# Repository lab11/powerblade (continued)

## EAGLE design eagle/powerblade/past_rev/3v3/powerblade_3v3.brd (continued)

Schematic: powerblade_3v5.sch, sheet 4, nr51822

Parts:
B1: BAL-NRF01D3
C11: 4.7uF; C0402; DIGIKEY 445-5947-1-ND
C12, C20: 1nF; 0402_CAP; DIGIKEY 490-1303-1-ND
C17: 1uF; 0402_CAP; DIGIKEY 1276-1513-1-ND
C18, C19: 12pF; 0402_CAP; DIGIKEY 490-6197-1-ND
C21: 47nF; 0402_CAP; DIGIKEY 445-1264-1-ND
C22: 2.2nF; 0402_CAP; DIGIKEY 490-5419-1-ND
C23: 0.8pF; 0402_CAP; DIGIKEY 490-6269-1-ND
C24: 0.1uF; C0402; DIGIKEY 445-4952-1-ND
J4: TC2030-JLINK-NL; TC2030-IDC-NL; DIGIKEY NP
L2: 15nH; 0402_CAP; DIGIKEY 587-1521-1-ND
L4: 10uH; C0603_TN; DIGIKEY 490-4025-1-ND
Q1: NTS4173; SC-70-3
R4: 12k; 0402_RES; DIGIKEY RHM12.0KCDCT-ND
R8: 220k; R0402_SM; DIGIKEY P220KJCT-ND
U4: NRF51822QF; QFN-48-6MM
X1: 16MHz; TXC-8Y; DIGIKEY 887-2003-1-ND
Y1: UREACH_XTEND

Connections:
+3V3: Q1.P2 (S), R8.2; also elsewhere on the board
AVDD: C12.1, C17.1, L2.1, U4.35 (AVDD), U4.36 (AVDD)
BLE_ENABLE: Q1.P1 (G), R8.1; also elsewhere on the board
BLE_LPINT: U4.9 (P05/AIN6); also elsewhere on the board
DCC: L4.2, U4.2 (DCC)
FROMBLE_RX: U4.48 (P29); also elsewhere on the board
unnamed: B1.SE, C23.1, Y1.P1
unnamed: B1.ANT1, U4.31 (ANT1)
unnamed: B1.ANT2, U4.32 (ANT2)
unnamed: L2.2, L4.1
unnamed: C18.1, U4.37 (XC1), X1.1
unnamed: C19.1, U4.38 (XC2), X1.3 (2)
unnamed: C20.1, U4.39 (DEC1)
unnamed: C21.1, U4.29 (DEC2)
SWDCLK: J4.4 (SWCLK), R4.1, U4.24 (SWDCLK)
SWDIO/!RESET: J4.2 (SWDIO), U4.23 (SWDIO/!RESET)
TOBLE_TX: U4.47 (P28); also elsewhere on the board
V+: C11.1, C24.1, J4.1 (VCC), Q1.P3 (D), U4.1 (VDD), U4.12 (VDD)
VDD_PA: B1.VCC (VDD_PA), C22.1, U4.30 (VDD_PA)

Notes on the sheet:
PIN12
PIN1
PIN36

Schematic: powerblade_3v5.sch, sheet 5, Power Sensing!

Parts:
C2: 0.1uF; C0402; DIGIKEY 490-10777-1-ND
C13: 0.1uF; 0402_CAP; DIGIKEY 445-4952-1-ND
C27, C38: 0.1uF; C0402; DIGIKEY 445-4952-1-ND
C39: 1.5uF; C0402; DIGIKEY 445-13815-1-ND
L3: L-USL0805; L0805; DIGIKEY 732-3452-1-ND
Q4: 2SK1829; SC-70-3
R2: 3k; R0402_SM; DIGIKEY P3.00KLCT-ND
R6: 660k; R0402; DIGIKEY P665KLCT-ND
R14: 200; R0402; DIGIKEY P200LCT-ND
R15, R20, R40: 1M 1%; R0402; DIGIKEY P1.00MLCT-ND
R16: 75 1%; R0402; DIGIKEY P75.0LCT-ND
R17: 1k 1%; R0402; DIGIKEY P1.00KLCT-ND
R18: 4.99 1%; R0402; DIGIKEY RMCF0402FT4R99CT-ND
R21: 1M 1%; R0402_SM; DIGIKEY P1.00MLCT-ND
R35: 20k; R0402; DIGIKEY P20.0KLCT-ND
R37: 887k 1%; R0402; DIGIKEY P887KLCT-ND
R38: 30k 1%; R0402; DIGIKEY P30.0KLCT-ND
R39: 16k 1%; R0402; DIGIKEY P16.0KLCT-ND
RF: 4.99k 1%; R0402; DIGIKEY P4.99KLCT-ND
RI1, RI2: 953k 1%; R0402; DIGIKEY P953KLCT-ND
U2: MCP6V3; SC70-5; DIGIKEY 296-19547-1-ND
U6: MAX9910; SC70-5; DIGIKEY 296-25252-1-ND
U7: OPA2369; SOT-23-8

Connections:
+3V3: C13.1, C27.1, C38.1, R15.1, R20.2, R40.2, U2.P5 (VCC), U6.P5 (VCC), U7.P8 (VCC); also elsewhere on the board
METER_ENABLE: Q4.P1 (G), R6.1; also elsewhere on the board
unnamed: R2.1, R37.2, U7.P7 (OUT)
unnamed 20: L3.2, R14.1, R15.2, R16.2; also elsewhere on the board
unnamed: L3.1, R14.2, U2.P1 (IN+)
unnamed: R20.1, R21.2, U6.P1 (IN+)
unnamed: RF.1, RI1.2, RI2.2, U6.P3 (IN-)
unnamed 25: R17.1, R18.2, U2.P3 (IN-); also elsewhere on the board
unnamed: R37.1, R38.2, U7.P6 (IN-)
unnamed: R35.1, U7.P1 (OUT), U7.P2 (IN-)
unnamed: R39.2, R40.1, U7.P3 (IN+)
VAMP: C39.1, R17.2, U2.P4 (OUT)
VFILT: C39.2, R35.2, U7.P5 (IN+); also elsewhere on the board
VTEST: RI1.1; also elsewhere on the board

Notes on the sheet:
Voltage offset
50uV offset
For zero offset:
R15=NP
R16=0
Current Measurement
Voltage Measurement
Output voltage:
-(RF/RI)*VTEST + VCC/2
R15=1M
R16=15

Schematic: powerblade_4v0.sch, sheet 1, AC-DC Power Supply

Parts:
C1: 33uF; CPOL0805_SM; DIGIKEY 478-8650-1-ND
C3: 22uF; C0603_SM; DIGIKEY 445-9077-1-ND
D1: ZENERBZT52; BZT52; DIGIKEY BZT52C10T-7DICT-ND
D2: DIODE; BAS521
J2: AC_INFINAL; AC3_FINAL; DIGIKEY ED1649-ND
R3: 69.8k; R1210; DIGIKEY P69.8KAACT-ND

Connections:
VCC: C1.+, C3.1, D2.C; also elsewhere on the board
VTEST: J2.PA.3, R3.1; also elsewhere on the board
ZC: D1.C, D2.A, R3.2; also elsewhere on the board

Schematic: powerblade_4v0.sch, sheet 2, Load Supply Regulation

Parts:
C4: 22pF; C0402; DIGIKEY 445-1239-1-ND
C5: NP; C0603_TN; DIGIKEY NP
C7: 4.7uF; C0402; DIGIKEY 445-8023-1-ND
C8: 0.1uF; C0402; DIGIKEY 445-4952-1-ND
C9: 0.1uF; C0402_SM; DIGIKEY 445-4952-1-ND
C10: 22uF; C0603_SM; DIGIKEY 445-9077-1-ND
L1: 10uH; L0805; DIGIKEY 490-4990-1-ND
R7: 560k; R0402; DIGIKEY P560KLCT-ND
R9: 180k; R0402; DIGIKEY P180KLCT-ND
R24: 1 1%; R0603_SM; DIGIKEY P1.0AJCT-ND
U1: TPS62122; WDFN-6

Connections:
+3V3: C5.1, R24.2; also elsewhere on the board
unnamed: L1.2, U1.P1 (SW)
unnamed: C4.2, R7.1, R9.2, U1.P3 (FB)
VCC: C7.1, C8.1, U1.P4 (EN), U1.P5 (VIN); also elsewhere on the board
VS+: C4.1, C9.1, C10.1, L1.1, R7.2, R24.1, U1.P2 (VOUT); also elsewhere on the board

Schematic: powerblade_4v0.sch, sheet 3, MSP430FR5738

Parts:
C6, C34: 8pF; C0402; DIGIKEY 445-4890-1-ND
C14: 0.1uF; C0402; DIGIKEY 445-4952-1-ND
C15: 10uF; C0603_SM; DIGIKEY 445-6853-1-ND
C16: 470nF; C0402; DIGIKEY 445-4989-1-ND
J1: JTAG_14PIN_IDC-ND; TC2050-IDC-NL-430-ND; DIGIKEY NP
R11, R22: 670k; R0402; DIGIKEY P665KLCT-ND
R12, R13: 330k; R0402; DIGIKEY P330KLCT-ND
R19: 47k; R0402; DIGIKEY P47KJCT-ND
U3: MSP430FR5738; VQFN-24
X3: 32.768kHz; 0805; DIGIKEY 535-12373-1-ND

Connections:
+3V3: C14.1, C15.1, J1.P2 (2), R19.2, U3.P20 (DVCC), U3.P24 (AVCC); also elsewhere on the board
BLE_ENABLE: U3.P16 (P1.6/TA0.0/UCBSDA/MOSI); also elsewhere on the board
BLE_LPINT: U3.P17 (P1.7/TA1.0/UCBSCL/MISO); also elsewhere on the board
FROMBLE_RX: U3.P14 (P2.1/TB0.0/UCARX/MISO); also elsewhere on the board
METER_ENABLE: U3.P15 (P2.2/UCBCLK); also elsewhere on the board
unnamed: C34.2, U3.P22 (XOUT), X3.1
unnamed: C16.2, U3.P18 (VCORE)
unnamed: C6.2, U3.P21 (XIN), X3.2
PWM_CURRENT: U3.P3 (P1.2/TA1.1/A2); also elsewhere on the board
PWM_VOLTAGE: U3.P4 (P1.3/TA1.2/A3); also elsewhere on the board
RST: J1.P10 (11), R19.1, U3.P12 (RST)
TCK: J1.P7 (7), U3.P10 (TCK)
TDI: J1.P3 (3), U3.P8 (TDI)
TDO: J1.P1 (1), R13.2, R22.1, U3.P7 (TDO)
TEST: J1.P8 (8), U3.P11 (TEST)
TMS: J1.P5 (5), U3.P9 (TMS)
TOBLE_TX: U3.P13 (P2.0/UCATX/MOSI); also elsewhere on the board
VCC: R11.2; also elsewhere on the board
VCC_SENSE: R11.1, R12.2, U3.P6 (P1.5/TB0.2/UCACLK)
VFILT: U3.P2 (P1.1/VREF+); also elsewhere on the board
ZC: R22.2; also elsewhere on the board

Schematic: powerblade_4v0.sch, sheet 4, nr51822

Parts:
B1: BAL-NRF01D3
C11: 4.7uF; C0402; DIGIKEY 445-5947-1-ND
C12, C20: 1nF; 0402_CAP; DIGIKEY 490-1303-1-ND
C17: 1uF; 0402_CAP; DIGIKEY 1276-1513-1-ND
C18, C19: 12pF; 0402_CAP; DIGIKEY 490-6197-1-ND
C21: 47nF; 0402_CAP; DIGIKEY 445-1264-1-ND
C22: 2.2nF; 0402_CAP; DIGIKEY 490-5419-1-ND
C23: 0.8pF; 0402_CAP; DIGIKEY 490-6269-1-ND
C24: 0.1uF; C0402; DIGIKEY 445-4952-1-ND
J4: TC2030-JLINK-NL; TC2030-IDC-NL; DIGIKEY NP
L2: 15nH; 0402_CAP; DIGIKEY 587-1521-1-ND
L4: 10uH; C0603_TN; DIGIKEY 490-4025-1-ND
Q1: NTS4173; SC-70-3
R4: 12k; 0402_RES; DIGIKEY RHM12.0KCDCT-ND
R8: 220k; R0402_SM; DIGIKEY P220KJCT-ND
U4: NRF51822QF; QFN-48-6MM
X1: 16MHz; TXC-8Y; DIGIKEY 887-2003-1-ND
Y1: UREACH_XTEND

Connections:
+3V3: Q1.P2 (S), R8.2; also elsewhere on the board
AVDD: C12.1, C17.1, L2.1, U4.35 (AVDD), U4.36 (AVDD)
BLE_ENABLE: Q1.P1 (G), R8.1; also elsewhere on the board
BLE_LPINT: U4.9 (P05/AIN6); also elsewhere on the board
DCC: L4.2, U4.2 (DCC)
FROMBLE_RX: U4.48 (P29); also elsewhere on the board
unnamed: B1.SE, C23.1, Y1.P1
unnamed: B1.ANT1, U4.31 (ANT1)
unnamed: B1.ANT2, U4.32 (ANT2)
unnamed: L2.2, L4.1
unnamed: C18.1, U4.37 (XC1), X1.1
unnamed: C19.1, U4.38 (XC2), X1.3 (2)
unnamed: C20.1, U4.39 (DEC1)
unnamed: C21.1, U4.29 (DEC2)
SWDCLK: J4.4 (SWCLK), R4.1, U4.24 (SWDCLK)
SWDIO/!RESET: J4.2 (SWDIO), U4.23 (SWDIO/!RESET)
TOBLE_TX: U4.47 (P28); also elsewhere on the board
V+: C11.1, C24.1, J4.1 (VCC), Q1.P3 (D), U4.1 (VDD), U4.12 (VDD)
VDD_PA: B1.VCC (VDD_PA), C22.1, U4.30 (VDD_PA)

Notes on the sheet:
PIN12
PIN1
PIN36

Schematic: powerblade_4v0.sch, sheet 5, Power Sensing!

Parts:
C2: 0.1uF; C0402; DIGIKEY 490-10777-1-ND
C13: 0.1uF; 0402_CAP; DIGIKEY 445-4952-1-ND
C27, C38: 0.1uF; C0402; DIGIKEY 445-4952-1-ND
C39: 1.5uF; C0402; DIGIKEY 445-13815-1-ND
L3: L-USL0805; L0805; DIGIKEY 732-3452-1-ND
Q4: 2SK1829; SC-70-3
R2: 3k; R0402_SM; DIGIKEY P3.00KLCT-ND
R6: 660k; R0402; DIGIKEY P665KLCT-ND
R14: 200; R0402; DIGIKEY P200LCT-ND
R15, R20, R40: 1M 1%; R0402; DIGIKEY P1.00MLCT-ND
R16: 75 1%; R0402; DIGIKEY P75.0LCT-ND
R17: 1k 1%; R0402; DIGIKEY P1.00KLCT-ND
R18: 4.99 1%; R0402; DIGIKEY RMCF0402FT4R99CT-ND
R21: 1M 1%; R0402_SM; DIGIKEY P1.00MLCT-ND
R35: 20k; R0402; DIGIKEY P20.0KLCT-ND
R37: 887k 1%; R0402; DIGIKEY P887KLCT-ND
R38: 30k 1%; R0402; DIGIKEY P30.0KLCT-ND
R39: 16k 1%; R0402; DIGIKEY P16.0KLCT-ND
RF: 4.99k 1%; R0402; DIGIKEY P4.99KLCT-ND
RI1, RI2: 953k 1%; R0402; DIGIKEY P953KLCT-ND
U2: MCP6V3; SC70-5; DIGIKEY 296-19547-1-ND
U6: MAX9910; SC70-5; DIGIKEY 296-25252-1-ND
U7: OPA2369; SOT-23-8

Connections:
+3V3: C13.1, C27.1, C38.1, R15.1, R20.2, R40.2, U2.P5 (VCC), U6.P5 (VCC), U7.P8 (VCC); also elsewhere on the board
METER_ENABLE: Q4.P1 (G), R6.1; also elsewhere on the board
unnamed: R2.1, R37.2, U7.P7 (OUT)
unnamed 20: L3.2, R14.1, R15.2, R16.2; also elsewhere on the board
unnamed: L3.1, R14.2, U2.P1 (IN+)
unnamed: R20.1, R21.2, U6.P1 (IN+)
unnamed: RF.1, RI1.2, RI2.2, U6.P3 (IN-)
unnamed 25: R17.1, R18.2, U2.P3 (IN-); also elsewhere on the board
unnamed: R37.1, R38.2, U7.P6 (IN-)
unnamed: R35.1, U7.P1 (OUT), U7.P2 (IN-)
unnamed: R39.2, R40.1, U7.P3 (IN+)
VAMP: C39.1, R17.2, U2.P4 (OUT)
VFILT: C39.2, R35.2, U7.P5 (IN+); also elsewhere on the board
VTEST: RI1.1; also elsewhere on the board

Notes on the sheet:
Voltage offset
50uV offset
For zero offset:
R15=NP
R16=0
Current Measurement
Voltage Measurement
Output voltage:
-(RF/RI)*VTEST + VCC/2
R15=1M
R16=15

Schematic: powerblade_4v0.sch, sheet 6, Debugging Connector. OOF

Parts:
SV1: MA12-11M27; MA12-1_1MM27; DIGIKEY S9014E-12-ND

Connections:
+3V3: SV1.P8 (8); also elsewhere on the board
FROMBLE_RX: SV1.P2 (2); also elsewhere on the board
PWM_CURRENT: SV1.P5 (5); also elsewhere on the board
PWM_VOLTAGE: SV1.P4 (4); also elsewhere on the board
TOBLE_TX: SV1.P1 (1); also elsewhere on the board
VCC: SV1.P10 (10); also elsewhere on the board
VFILT: SV1.P9 (9); also elsewhere on the board
VS+: SV1.P12 (12); also elsewhere on the board
ZC: SV1.P11 (11); also elsewhere on the board

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
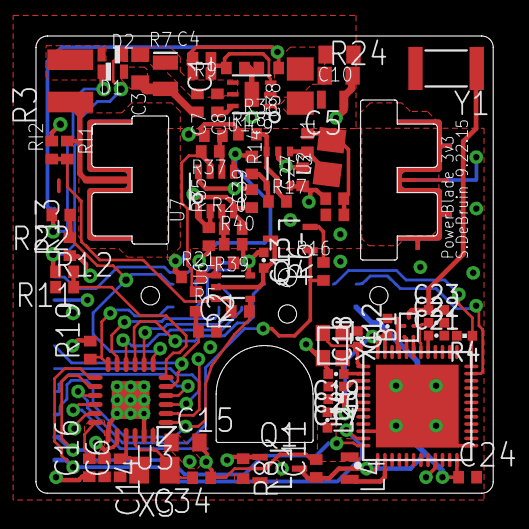
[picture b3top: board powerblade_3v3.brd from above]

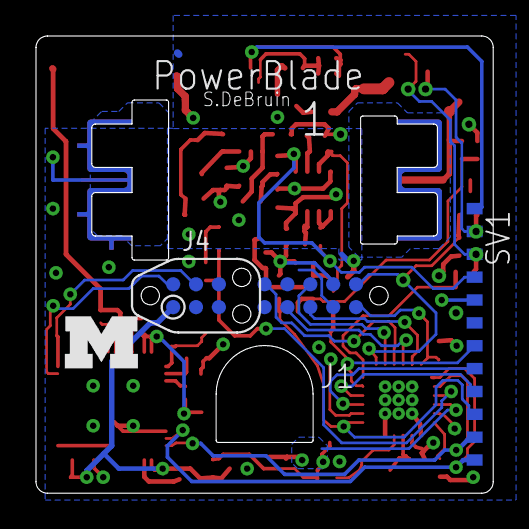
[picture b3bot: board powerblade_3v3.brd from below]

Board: 4 copper layers, 25.4 x 25.4 mm, 79 parts (4 on the bottom side), 53 nets.

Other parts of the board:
U$1: BLOCK-M

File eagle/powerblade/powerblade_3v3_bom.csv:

"Part";"Value";"Device";"Package";"Description";"DIGIKEY";"DIGIKEY_2";"DIGIKEY_3";"DIGIKEY_4";"FRACTUS";"MOUSER";
"B1";"BAL-NRF01D3";"BAL-NRF01D3";"BAL-NRF01D3";"50 ohm nominal input / conjugate match balun to nRF51422-QFAA,";"497-13637-1-ND";"";"";"";"";"511-BAL-NRF01D3";
"C1";"33uF";"CPOL-US0805_SM";"CPOL0805_SM";"POLARIZED CAPACITOR, American symbol";"478-8650-1-ND";"";"";"";"";"";
"C2";"0.1uF";"C-EUC0402";"C0402";"CAPACITOR, European symbol";"490-10777-1-ND";"";"";"";"";"";
"C3";"22uF";"C-EUC0603_SM";"C0603_SM";"CAPACITOR, European symbol";"445-9077-1-ND";"";"";"";"";"";
"C4";"22pF";"C-EUC0402";"C0402";"CAPACITOR, European symbol";"445-1239-1-ND";"";"";"";"";"";
"C5";"NP";"C-EUC0603_TN";"C0603_TN";"CAPACITOR, European symbol";"NP";"";"";"";"";"";
"C6";"8pF";"C-EUC0402";"C0402";"CAPACITOR, European symbol";"445-4890-1-ND";"";"";"";"";"";
"C7";"4.7uF";"C-EUC0402";"C0402";"CAPACITOR, European symbol";"445-8023-1-ND";"";"";"";"";"";
"C8";"0.1uF";"C-EUC0402";"C0402";"CAPACITOR, European symbol";"445-4952-1-ND";"";"";"";"";"";
"C9";"0.1uF";"C-EUC0402_SM";"C0402_SM";"CAPACITOR, European symbol";"445-4952-1-ND";"";"";"";"";"";
"C10";"22uF";"C-EUC0603_SM";"C0603_SM";"CAPACITOR, European symbol";"445-9077-1-ND";"";"";"";"";"";
"C11";"4.7uF";"C-EUC0402";"C0402";"CAPACITOR, European symbol";"445-5947-1-ND";"";"";"";"";"";
"C12";"1nF";"CAPACITOR";"0402_CAP";"0402 Capacitor";"490-1303-1-ND";"";"";"";"";"";
"C13";"0.1uF";"CAPACITOR";"0402_CAP";"0402 Capacitor";"445-4952-1-ND";"";"";"";"";"";
"C14";"0.1uF";"C-EUC0402";"C0402";"CAPACITOR, European symbol";"445-4952-1-ND";"";"";"";"";"";
"C15";"10uF";"C-EUC0603_SM";"C0603_SM";"CAPACITOR, European symbol";"445-6853-1-ND";"";"";"";"";"";
"C16";"470nF";"C-EUC0402";"C0402";"CAPACITOR, European symbol";"445-4989-1-ND";"";"";"";"";"";
"C17";"1uF";"CAPACITOR";"0402_CAP";"0402 Capacitor";"1276-1513-1-ND";"";"";"";"";"";
"C18";"12pF";"CAPACITOR";"0402_CAP";"0402 Capacitor";"490-6197-1-ND";"";"";"";"";"";
"C19";"12pF";"CAPACITOR";"0402_CAP";"0402 Capacitor";"490-6197-1-ND";"";"";"";"";"";
"C20";"1nF";"CAPACITOR";"0402_CAP";"0402 Capacitor";"490-1303-1-ND";"";"";"";"";"";
"C21";"47nF";"CAPACITOR";"0402_CAP";"0402 Capacitor";"445-1264-1-ND";"";"";"";"";"";
"C22";"2.2nF";"CAPACITOR";"0402_CAP";"0402 Capacitor";"490-5419-1-ND";"";"";"";"";"";
"C23";"0.8pF";"CAPACITOR";"0402_CAP";"0402 Capacitor";"490-6269-1-ND";"";"";"";"";"";
"C24";"0.1uF";"C-EUC0402";"C0402";"CAPACITOR, European symbol";"445-4952-1-ND";"";"";"";"";"";
"C27";"0.1uF";"C-EUC0402";"C0402";"CAPACITOR, European symbol";"445-4952-1-ND";"";"";"";"";"";
"C34";"8pF";"C-EUC0402";"C0402";"CAPACITOR, European symbol";"445-4890-1-ND";"";"";"";"";"";
"C38";"0.1uF";"C-EUC0402";"C0402";"CAPACITOR, European symbol";"445-4952-1-ND";"";"";"";"";"";
"C39";"1.5uF";"C-EUC0402";"C0402";"CAPACITOR, European symbol";"445-13815-1-ND";"";"";"";"";"";
"D1";"ZENERBZT52";"ZENERBZT52";"BZT52";"";"BZT52C10T-7DICT-ND ";"";"";"";"";"";
"D2";"DIODE";"DIODE";"BAS521";"";"BAS521-7DICT-ND";"";"";"";"";"";
"J1";"JTAG_14PIN_IDC-ND";"JTAG_14PIN_IDC-ND";"TC2050-IDC-NL-430-ND";"";"NP";"";"";"";"";"";
"J2";"AC_INF45";"AC_INF45";"AC3_F45";"";"ED1649-ND";"ED1649-ND";"ED1649-ND";"ED1649-ND";"";"";
"J4";"TC2030-JLINK-NL";"TC2030-JLINK-NL";"TC2030-IDC-NL";"";"NP";"";"";"";"";"";
"L1";"10uH";"L-USL0805";"L0805";"INDUCTOR, American symbol";"490-4990-1-ND";"";"";"";"";"";
"L2";"15nH";"INDUCTOR0402";"0402_CAP";"";"587-1521-1-ND";"";"";"";"";"";
"L3";"";"L-USL0805";"L0805";"INDUCTOR, American symbol";"732-3452-1-ND";"";"";"";"";"";
"L4";"10uH";"L-USL0603_TN";"C0603_TN";"INDUCTOR, American symbol";"490-4025-1-ND";"";"";"";"";"";
"Q1";"NTS4173";"NTS4173";"SC-70-3";"";"NTS4173PT1GOSCT-ND";"";"";"";"";"";
"Q4";"2SK1829";"2SK1829";"SC-70-3";"";"2SK1829TE85LFCT-ND";"";"";"";"";"";
"R2";"3k";"R-US_R0402_SM";"R0402_SM";"RESISTOR, American symbol";"P3.00KLCT-ND";"";"";"";"";"";
"R3";"69.8k";"R-US_R1210";"R1210";"RESISTOR, American symbol";"P69.8KAACT-ND";"";"";"";"";"";
"R4";"12k";"RESISTOR";"0402_RES";"Resistor";"RHM12.0KCDCT-ND";"";"";"";"";"";
"R6";"660k";"R-US_R0402";"R0402";"RESISTOR, American symbol";"P665KLCT-ND";"";"";"";"";"";
"R7";"560k";"R-US_R0402";"R0402";"RESISTOR, American symbol";"P560KLCT-ND";"";"";"";"";"";
"R8";"220k";"R-US_R0402_SM";"R0402_SM";"RESISTOR, American symbol";"P220KJCT-ND";"";"";"";"";"";
"R9";"180k";"R-US_R0402";"R0402";"RESISTOR, American symbol";"P180KLCT-ND";"";"";"";"";"";
"R11";"670k";"R-US_R0402";"R0402";"RESISTOR, American symbol";"P665KLCT-ND";"";"";"";"";"";
"R12";"330k";"R-US_R0402";"R0402";"RESISTOR, American symbol";"P330KLCT-ND";"";"";"";"";"";
"R13";"330k";"R-US_R0402";"R0402";"RESISTOR, American symbol";"P330KLCT-ND";"";"";"";"";"";
"R14";"200";"R-US_R0402";"R0402";"RESISTOR, American symbol";"P200LCT-ND";"";"";"";"";"";
"R15";"1M 1%";"R-US_R0402";"R0402";"RESISTOR, American symbol";"P1.00MLCT-ND";"";"";"";"";"";
"R16";"75 1%";"R-US_R0402";"R0402";"RESISTOR, American symbol";"P75.0LCT-ND";"";"";"";"";"";
"R17";"1k 1%";"R-US_R0402";"R0402";"RESISTOR, American symbol";"P1.00KLCT-ND";"";"";"";"";"";
"R18";"4.99 1%";"R-US_R0402";"R0402";"RESISTOR, American symbol";"RMCF0402FT4R99CT-ND";"";"";"";"";"";
"R19";"47k";"R-US_R0402";"R0402";"RESISTOR, American symbol";"P47KJCT-ND";"";"";"";"";"";
"R20";"1M 1%";"R-US_R0402";"R0402";"RESISTOR, American symbol";"P1.00MLCT-ND";"";"";"";"";"";
"R21";"1M 1%";"R-US_R0402_SM";"R0402_SM";"RESISTOR, American symbol";"P1.00MLCT-ND";"";"";"";"";"";
"R22";"670k";"R-US_R0402";"R0402";"RESISTOR, American symbol";"P665KLCT-ND";"";"";"";"";"";
"R24";"1 1%";"R-US_R0603_SM";"R0603_SM";"RESISTOR, American symbol";"P1.0AJCT-ND";"";"";"";"";"";
"R35";"20k";"R-US_R0402";"R0402";"RESISTOR, American symbol";"P20.0KLCT-ND";"";"";"";"";"";
"R37";"887k 1%";"R-US_R0402";"R0402";"RESISTOR, American symbol";"P887KLCT-ND";"";"";"";"";"";
"R38";"30k 1%";"R-US_R0402";"R0402";"RESISTOR, American symbol";"P30.0KLCT-ND";"";"";"";"";"";
"R39";"16k 1%";"R-US_R0402";"R0402";"RESISTOR, American symbol";"P16.0KLCT-ND";"";"";"";"";"";
"R40";"1M 1%";"R-US_R0402";"R0402";"RESISTOR, American symbol";"P1.00MLCT-ND";"";"";"";"";"";
"RF";"4.99k 1%";"R-US_R0402";"R0402";"RESISTOR, American symbol";"P4.99KLCT-ND";"";"";"";"";"";
"RI1";"953k 1%";"R-US_R0402";"R0402";"RESISTOR, American symbol";"P953KLCT-ND";"";"";"";"";"";
"RI2";"953k 1%";"R-US_R0402";"R0402";"RESISTOR, American symbol";"P953KLCT-ND";"";"";"";"";"";
"SV1";"";"MA12-11M27";"MA12-1_1MM27";"PIN HEADER";"S9014E-12-ND";"";"";"";"";"";
"U1";"TPS62122";"TPS62122";"WDFN-6";"";"296-27695-1-ND";"";"";"";"";"";
"U2";"MCP6V3";"MCP6V3";"SC70-5";"";"296-19547-1-ND";"";"";"";"";"";
"U3";"MSP430FR5738";"MSP430FR5738";"VQFN-24";"";"296-29232-1-ND";"";"";"";"";"";
"U4";"NRF51822QF";"NRF51822QF";"QFN-48-6MM";"Multiprotocol Bluetooth® 4.0 low energy/2.4 GHz RF SoC";"1490-1032-1-ND";"";"";"";"";"949-NRF51822-QFAB-R7";
"U6";"MAX9910";"MAX9910";"SC70-5";"";"296-25252-1-ND";"";"";"";"";"";
"U7";"OPA2369";"OPA2369";"SOT-23-8";"";"296-22671-1-ND";"";"";"";"";"";
"X1";"16MHz";"TXC-8Y";"TXC-8Y";"2mmx1.6mm SMD Crystal";"887-2003-1-ND";"";"";"";"";"";
"X3";"32.768kHz";"CRYSTAL_0805";"0805";"";"535-12373-1-ND";"";"";"";"";"";
"Y1";"UREACH_XTEND";"UREACH_XTEND";"UREACH_XTEND";"";"";"";"";"";"FR05-S1-N-0-110";"";

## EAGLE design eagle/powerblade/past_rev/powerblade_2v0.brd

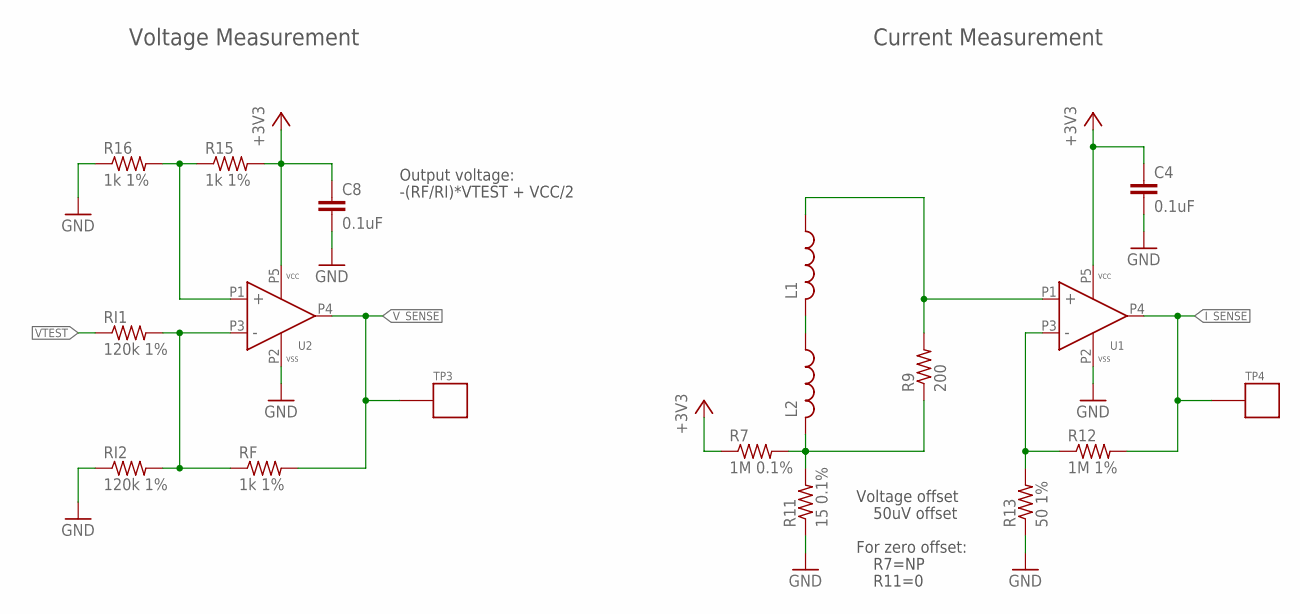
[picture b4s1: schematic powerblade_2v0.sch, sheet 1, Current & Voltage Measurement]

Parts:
C4, C8: 0.1uF; C0402; DIGIKEY 445-1265-1-ND
L1, L2: L-USL0805; L0805
R7: 1M 0.1%; R0603; DIGIKEY A102234CT-ND
R9: 200; R0603; DIGIKEY P200HCT-ND
R11: 15 0.1%; R0603; DIGIKEY A109933CT-ND
R12: 1M 1%; R0603; DIGIKEY A102234CT-ND
R13: 50 1%; R0603; DIGIKEY P49.9HCT-ND
R15, R16: 1k 1%; R0603; DIGIKEY P1.00KHCT-ND
RF: 1k 1%; R0603; DIGIKEY P1.00KHCT-ND
RI1, RI2: 120k 1%; R0603; DIGIKEY P120KHCT-ND
TP3, TP4: TP_STD; TP
U1, U2: MAX9910; SC70-5

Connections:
+3V3: C4.1, C8.1, R7.1, R15.2, U1.P5 (VCC), U2.P5 (VCC); also elsewhere on the board
GND: C4.2, C8.2, R11.1, R13.1, R16.1, RI2.1, U1.P2 (VSS), U2.P2 (VSS); also elsewhere on the board
I_SENSE: R12.2, TP4.P$1, U1.P4 (OUT); also elsewhere on the board
unnamed: R15.1, R16.2, U2.P1 (IN+)
unnamed: R12.1, R13.2, U1.P3 (IN-)
unnamed: RF.1, RI1.2, RI2.2, U2.P3 (IN-)
unnamed: L2.2, R7.2, R9.1, R11.2
unnamed: L1.1, R9.2, U1.P1 (IN+)
unnamed: L1.2, L2.1
VTEST: RI1.1; also elsewhere on the board
V_SENSE: RF.2, TP3.P$1, U2.P4 (OUT); also elsewhere on the board

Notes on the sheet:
Voltage offset
50uV offset
For zero offset:
R7=NP
R11=0
Current Measurement
Voltage Measurement
Output voltage:
-(RF/RI)*VTEST + VCC/2

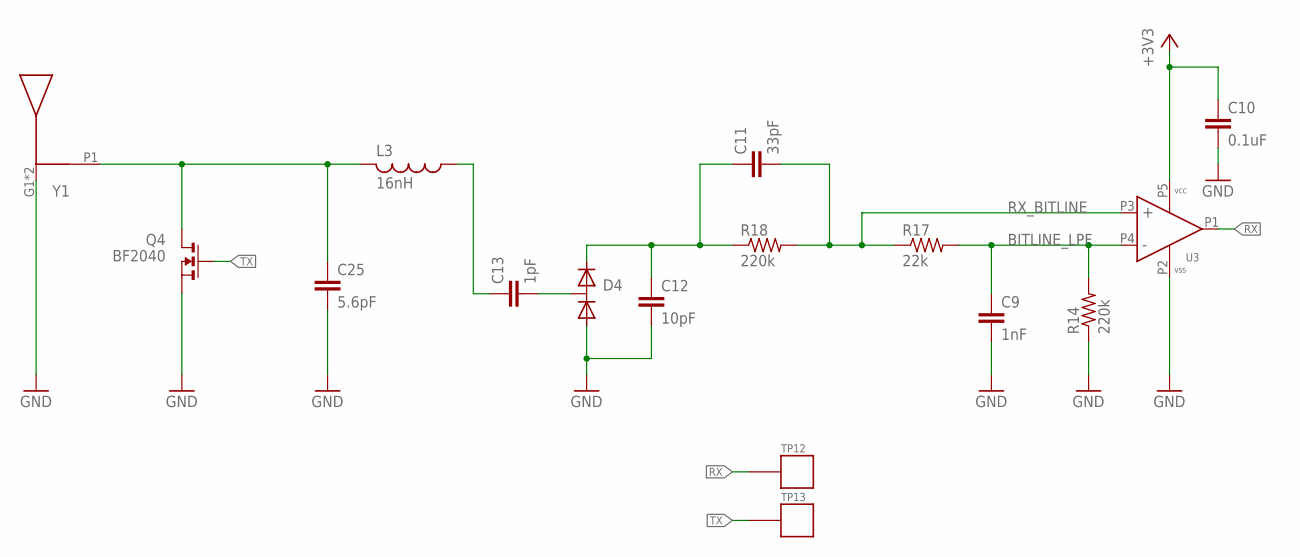
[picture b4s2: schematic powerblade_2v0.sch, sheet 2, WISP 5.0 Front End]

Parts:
C9: 1nF; C0603; DIGIKEY 490-6377-1-ND
C10: 0.1uF; C0603; DIGIKEY 445-1316-1-ND
C11: 33pF; C0603; DIGIKEY 399-7894-1-ND
C12: 10pF; C0603; DIGIKEY 1276-2151-1-ND
C13: 1pF; C0603; DIGIKEY 712-1323-1-ND
C25: 5.6pF; C0603; DIGIKEY 712-1360-1-ND
D4: HSMS-285C; SOT-323
L3: 16nH; L0603; DIGIKEY 732-1728-1-ND
Q4: BF2040; SOT-143
R14, R18: 220k; R0603; DIGIKEY P220KDBCT-ND
R17: 22k; R0603; DIGIKEY P22KDBCT-ND
TP12, TP13: TP_STD; TP
U3: NCS2200S; SC70-5
Y1: ANT-USP; DIGIKEY ANT-916-USP-ND

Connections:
+3V3: C10.1, U3.P5 (VCC); also elsewhere on the board
ANT: C25.1, L3.2, Q4.P2 (D), Y1.P1
BITLINE_LPF: C9.1, R14.2, R17.2, U3.P4 (IN-)
GND: C9.2, C10.2, C12.2, C25.2, D4.P1, Q4.P1 (S), R14.1, U3.P2 (VSS), Y1.G1 (G), Y1.G2 (G); also elsewhere on the board
unnamed: C13.1, L3.1
unnamed: C13.2, D4.P3
unnamed: C11.1, C12.1, D4.P2, R18.1
RX: TP12.P$1, U3.P1 (OUT); also elsewhere on the board
RX_BITLINE: C11.2, R17.1, R18.2, U3.P3 (IN+)
TX: Q4.P3 (G), Q4.P4 (G), TP13.P$1; also elsewhere on the board

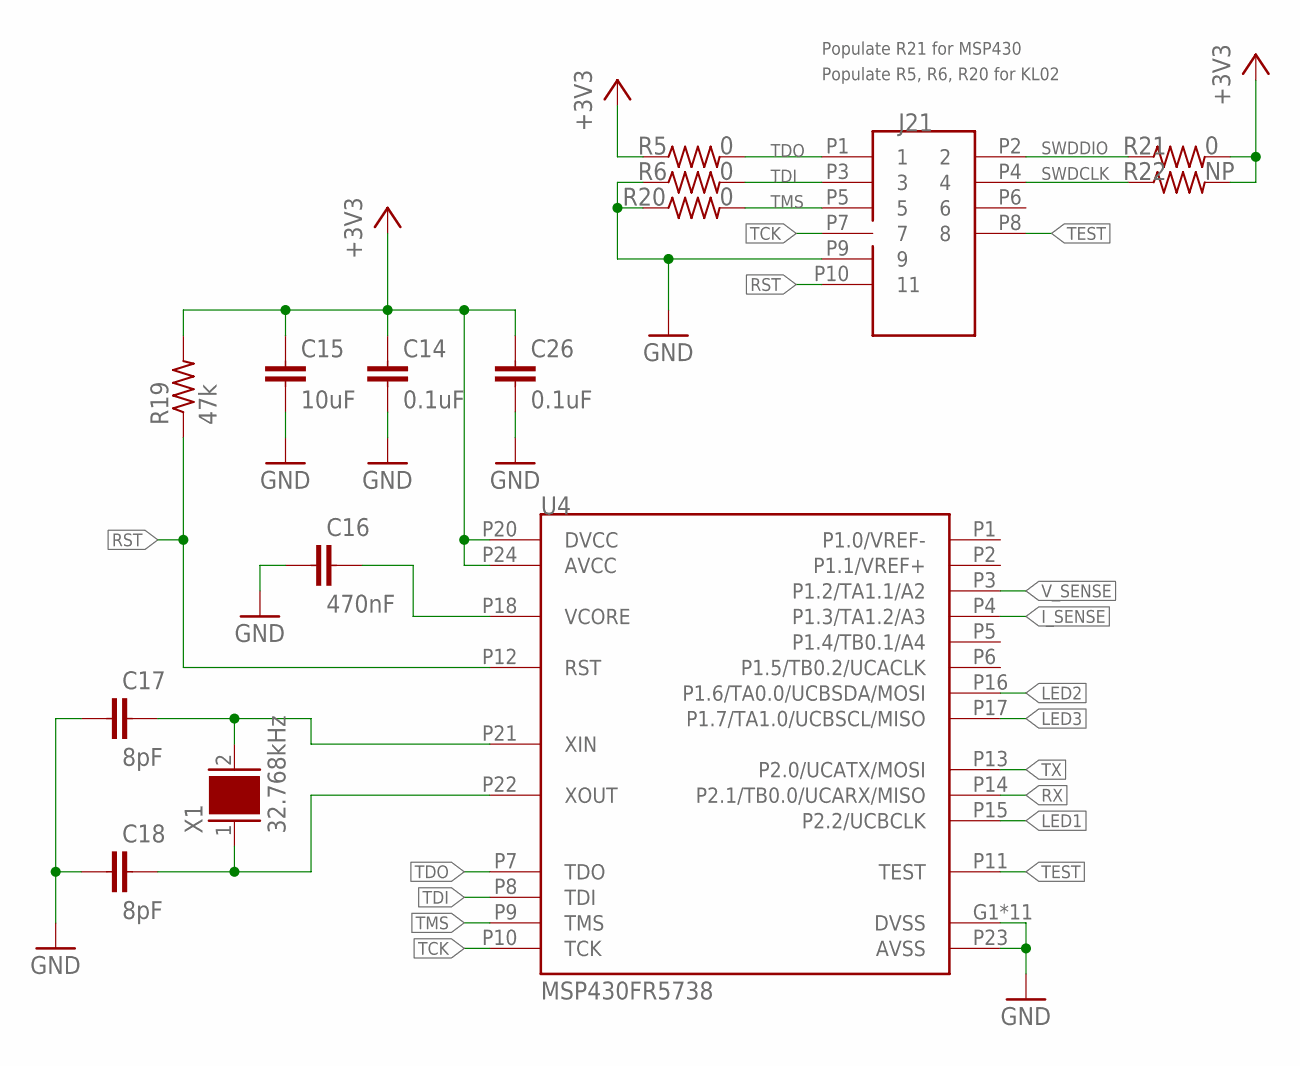
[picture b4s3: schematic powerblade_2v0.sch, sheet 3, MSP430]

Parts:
C14, C26: 0.1uF; C0603; DIGIKEY 445-1316-1-ND
C15: 10uF; C0603; DIGIKEY 1276-1119-1-ND
C16: 470nF; C0603; DIGIKEY 445-5192-1-ND
C17, C18: 8pF; C0603; DIGIKEY 1276-1817-1-ND
J21: JTAG_14PIN_IDC-NL; TC2050-IDC-NL-430; DIGIKEY NP
R5, R6, R20, R21: 0; R0603; DIGIKEY P0.0GCT-ND
R19: 47k; R0603; DIGIKEY P47KGCT-ND
R22: NP; R0603; DIGIKEY NP
U4: MSP430FR5738; VQFN-24
X1: 32.768kHz; 0805; DIGIKEY 535-12373-1-ND

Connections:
+3V3: C14.1, C15.1, C26.1, R5.1, R19.2, R21.2, R22.2, U4.P20 (DVCC), U4.P24 (AVCC); also elsewhere on the board
GND: C14.2, C15.2, C16.1, C17.1, C18.1, C26.2, J21.P9 (9), R6.1, R20.1, U4.G1 (DVSS), U4.G2 (DVSS), U4.G3 (DVSS), U4.G4 (DVSS), U4.G5 (DVSS), U4.G6 (DVSS), U4.G7 (DVSS), U4.G8 (DVSS), U4.G9 (DVSS), U4.P19 (DVSS), U4.P23 (AVSS), U4.PAD (DVSS); also elsewhere on the board
I_SENSE: U4.P4 (P1.3/TA1.2/A3); also elsewhere on the board
LED1: U4.P15 (P2.2/UCBCLK); also elsewhere on the board
LED2: U4.P16 (P1.6/TA0.0/UCBSDA/MOSI); also elsewhere on the board
LED3: U4.P17 (P1.7/TA1.0/UCBSCL/MISO); also elsewhere on the board
unnamed: C18.2, U4.P22 (XOUT), X1.1
unnamed: C16.2, U4.P18 (VCORE)
unnamed: C17.2, U4.P21 (XIN), X1.2
RST: J21.P10 (11), R19.1, U4.P12 (RST); also elsewhere on the board
RX: U4.P14 (P2.1/TB0.0/UCARX/MISO); also elsewhere on the board
SWDCLK: J21.P4 (4), R22.1; also elsewhere on the board
SWDDIO: J21.P2 (2), R21.1; also elsewhere on the board
TCK: J21.P7 (7), U4.P10 (TCK)
TDI: J21.P3 (3), R6.2, U4.P8 (TDI)
TDO: J21.P1 (1), R5.2, U4.P7 (TDO)
TEST: J21.P8 (8), U4.P11 (TEST)
TMS: J21.P5 (5), R20.2, U4.P9 (TMS)
TX: U4.P13 (P2.0/UCATX/MOSI); also elsewhere on the board
V_SENSE: U4.P3 (P1.2/TA1.1/A2); also elsewhere on the board

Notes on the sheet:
Populate R21 for MSP430
Populate R5, R6, R20 for KL02

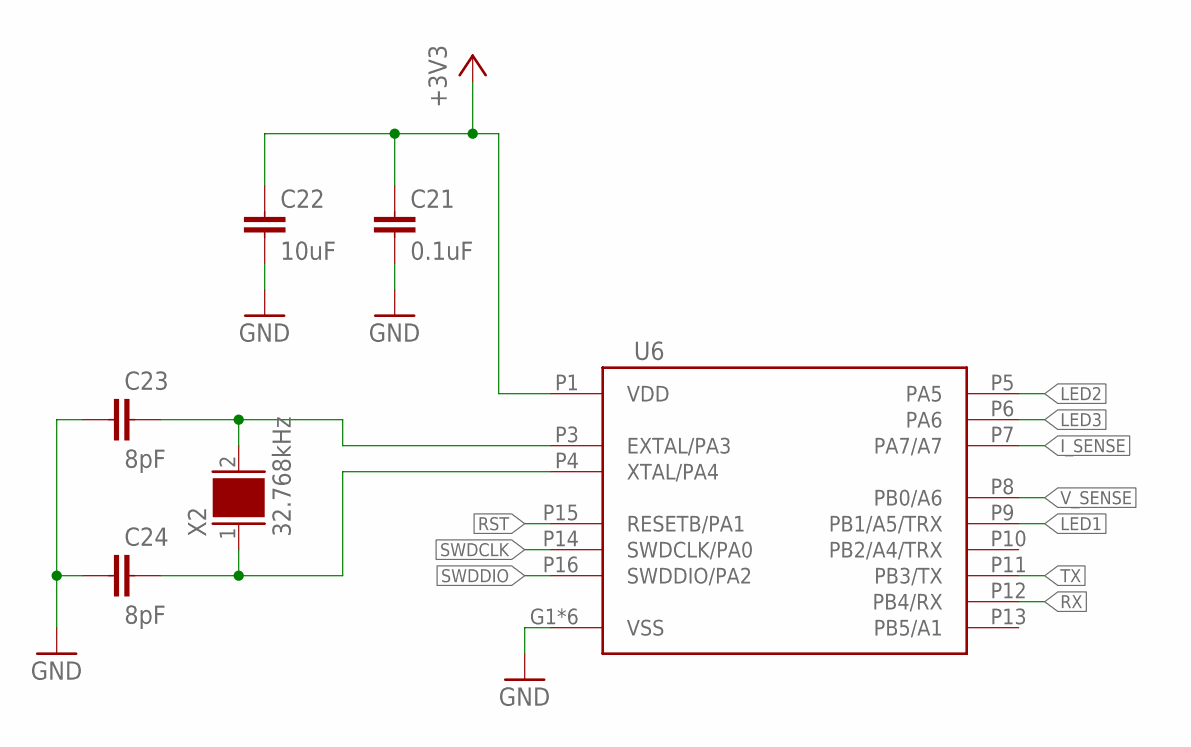
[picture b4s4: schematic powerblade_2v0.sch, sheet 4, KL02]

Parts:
C21: 0.1uF; C0603; DIGIKEY 445-1316-1-ND
C22: 10uF; C0603; DIGIKEY 1276-1119-1-ND
C23, C24: 8pF; C0603; DIGIKEY 1276-1817-1-ND
U6: KL02; WQFN-16
X2: 32.768kHz; 0805; DIGIKEY 535-12373-1-ND

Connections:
+3V3: C21.1, C22.1, U6.P1 (VDD); also elsewhere on the board
GND: C21.2, C22.2, C23.1, C24.1, U6.G1 (VSS), U6.G3 (VSS), U6.G7 (VSS), U6.G9 (VSS), U6.P2 (VSS), U6.PAD (VSS); also elsewhere on the board
I_SENSE: U6.P7 (PA7/A7); also elsewhere on the board
LED1: U6.P9 (PB1/A5/TRX); also elsewhere on the board
LED2: U6.P5 (PA5); also elsewhere on the board
LED3: U6.P6 (PA6); also elsewhere on the board
unnamed: C24.2, U6.P4 (XTAL/PA4), X2.1
unnamed: C23.2, U6.P3 (EXTAL/PA3), X2.2
RST: U6.P15 (RESETB/PA1); also elsewhere on the board
RX: U6.P12 (PB4/RX); also elsewhere on the board
SWDCLK: U6.P14 (SWDCLK/PA0); also elsewhere on the board
SWDDIO: U6.P16 (SWDDIO/PA2); also elsewhere on the board
TX: U6.P11 (PB3/TX); also elsewhere on the board
V_SENSE: U6.P8 (PB0/A6); also elsewhere on the board

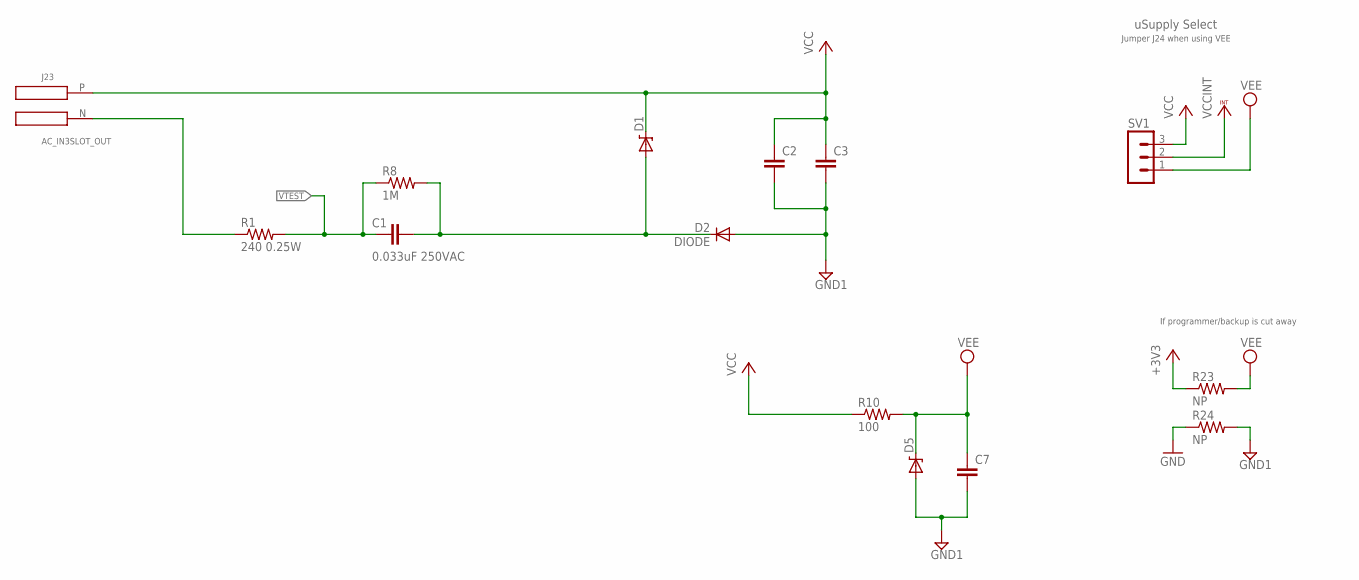
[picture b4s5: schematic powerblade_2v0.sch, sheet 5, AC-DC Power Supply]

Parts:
C1: 0.033uF 250VAC; C2220K; DIGIKEY 490-4238-1-ND
C2: C-EUC0805; C0805; DIGIKEY 445-8238-1-ND
C3: C-EUC0603; C0603; DIGIKEY 445-9077-1-ND
C7: C-EUC0603; C0603; DIGIKEY 1276-2383-1-ND
D1: ZENERBZT52; BZT52; DIGIKEY_2 BZT585B5V1T-7DICT-ND
D2: DIODE; BAS521
D5: ZENERBZT52; BZT52
J23: AC_IN3SLOT_OUT; AC3_SLOT_OUT; DIGIKEY 3M11307-ND
R1: 240 0.25W; R0603; DIGIKEY RHM240DCT-ND
R8: 1M; R0603; DIGIKEY MCT0603-1.00M-CFCT-ND
R10: 100; R0603; DIGIKEY P100GCT-ND
R23, R24: NP; R0603; DIGIKEY NP
SV1: MA03-1STR; MA03-1; DIGIKEY 3M9448-ND

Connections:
+3V3: R23.1; also elsewhere on the board
GND: R24.1; also elsewhere on the board
GND1: C2.2, C3.2, C7.2, D2.A, D5.A, R24.2; also elsewhere on the board
unnamed: J23.N, R1.1
unnamed: C1.1, D1.A, D2.C, R8.2
VCC: C2.1, C3.1, D1.C, J23.P, R10.1, SV1.3
VCCINT: SV1.2; also elsewhere on the board
VEE: C7.1, D5.C, R10.2, R23.2, SV1.1
VTEST: C1.2, R1.2, R8.1; also elsewhere on the board

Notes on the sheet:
uSupply Select
Jumper J24 when using VEE
If programmer/backup is cut away

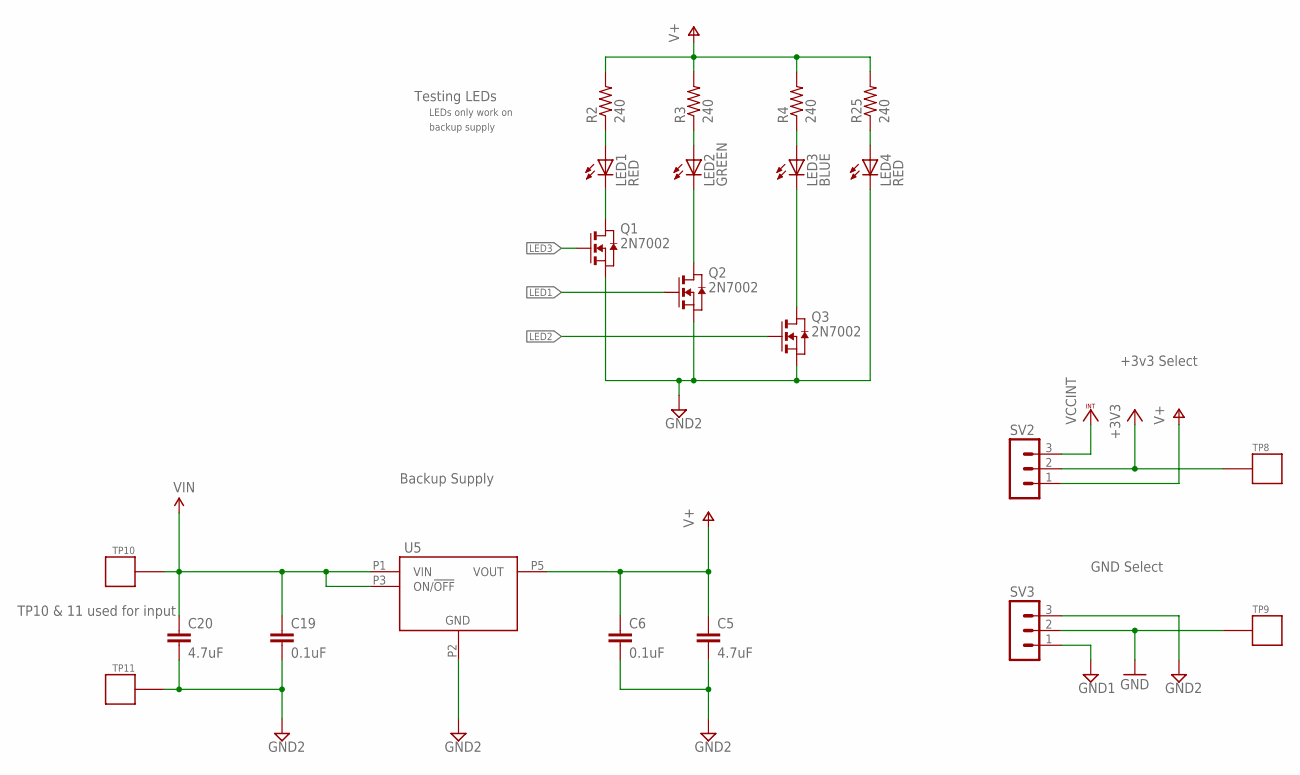
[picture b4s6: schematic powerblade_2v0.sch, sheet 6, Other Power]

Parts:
C5, C20: 4.7uF; C0603; DIGIKEY 490-3302-1-ND
C6, C19: 0.1uF; C0603; DIGIKEY 445-1316-1-ND
LED1, LED4: RED; LED-0603; DIGIKEY 1080-1400-1-ND
LED2: GREEN; LED-0603; DIGIKEY 1080-1402-1-ND
LED3: BLUE; LED-0603; DIGIKEY 1080-1401-1-ND
Q1, Q2, Q3: 2N7002; SC-70-3
R2, R3, R4, R25: 240; R0603; DIGIKEY P240GCT-ND
SV2, SV3: MA03-1STR; MA03-1; DIGIKEY 3M9448-ND
TP8, TP9, TP10, TP11: TP_STD; TP
U5: LP2980; SOT-23-5

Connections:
+3V3: SV2.2, TP8.P$1; also elsewhere on the board
GND: SV3.2, TP9.P$1; also elsewhere on the board
GND1: SV3.1; also elsewhere on the board
GND2: C5.2, C6.2, C19.2, C20.2, LED4.C, Q1.P2 (S), Q2.P2 (S), Q3.P2 (S), SV3.3, TP11.P$1, U5.P2 (GND)
LED1: Q2.P1 (G); also elsewhere on the board
LED2: Q3.P1 (G); also elsewhere on the board
LED3: Q1.P1 (G); also elsewhere on the board
unnamed: LED1.A, R2.1
unnamed: LED1.C, Q1.P3 (D)
unnamed: LED2.C, Q2.P3 (D)
unnamed: LED2.A, R3.1
unnamed: LED3.A, R4.1
unnamed: LED3.C, Q3.P3 (D)
unnamed: LED4.A, R25.1
V+: C5.1, C6.1, R2.2, R3.2, R4.2, R25.2, SV2.1, U5.P5 (VOUT)
VCCINT: SV2.3; also elsewhere on the board
VIN: C19.1, C20.1, TP10.P$1, U5.P1 (VIN), U5.P3 (ON/!OFF!)

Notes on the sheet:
+3v3 Select
GND Select
Backup Supply
Testing LEDs
LEDs only work on
backup supply
TP10 & 11 used for input

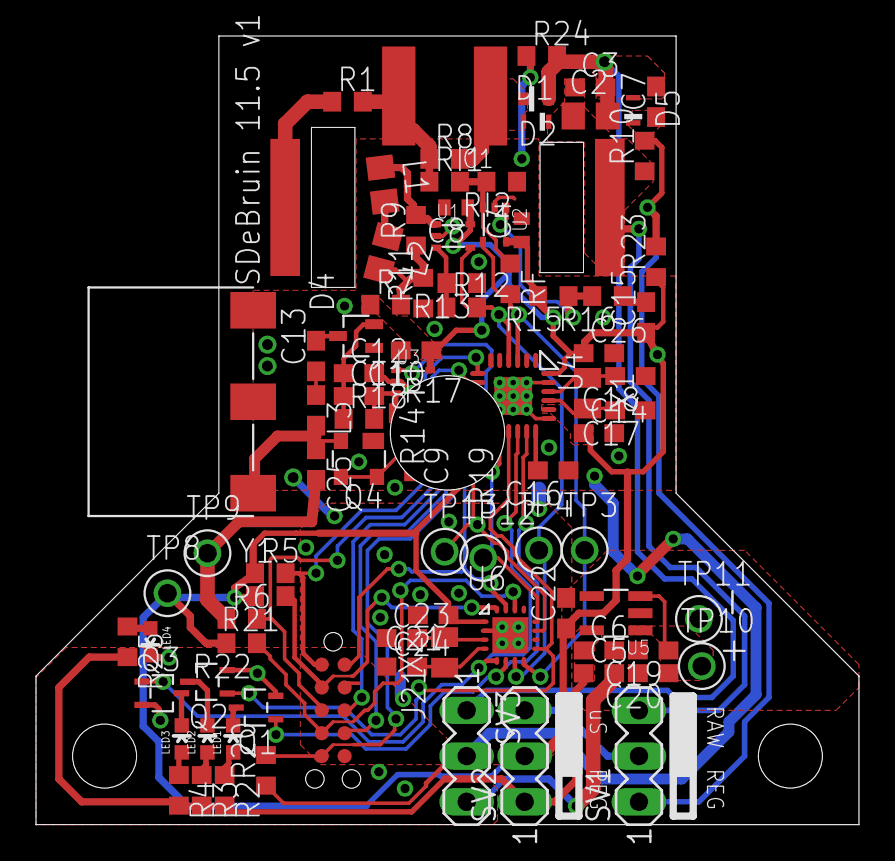
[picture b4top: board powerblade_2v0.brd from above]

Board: 2 copper layers, 45.7 x 43.8 mm, 91 parts (0 on the bottom side), 51 nets.
